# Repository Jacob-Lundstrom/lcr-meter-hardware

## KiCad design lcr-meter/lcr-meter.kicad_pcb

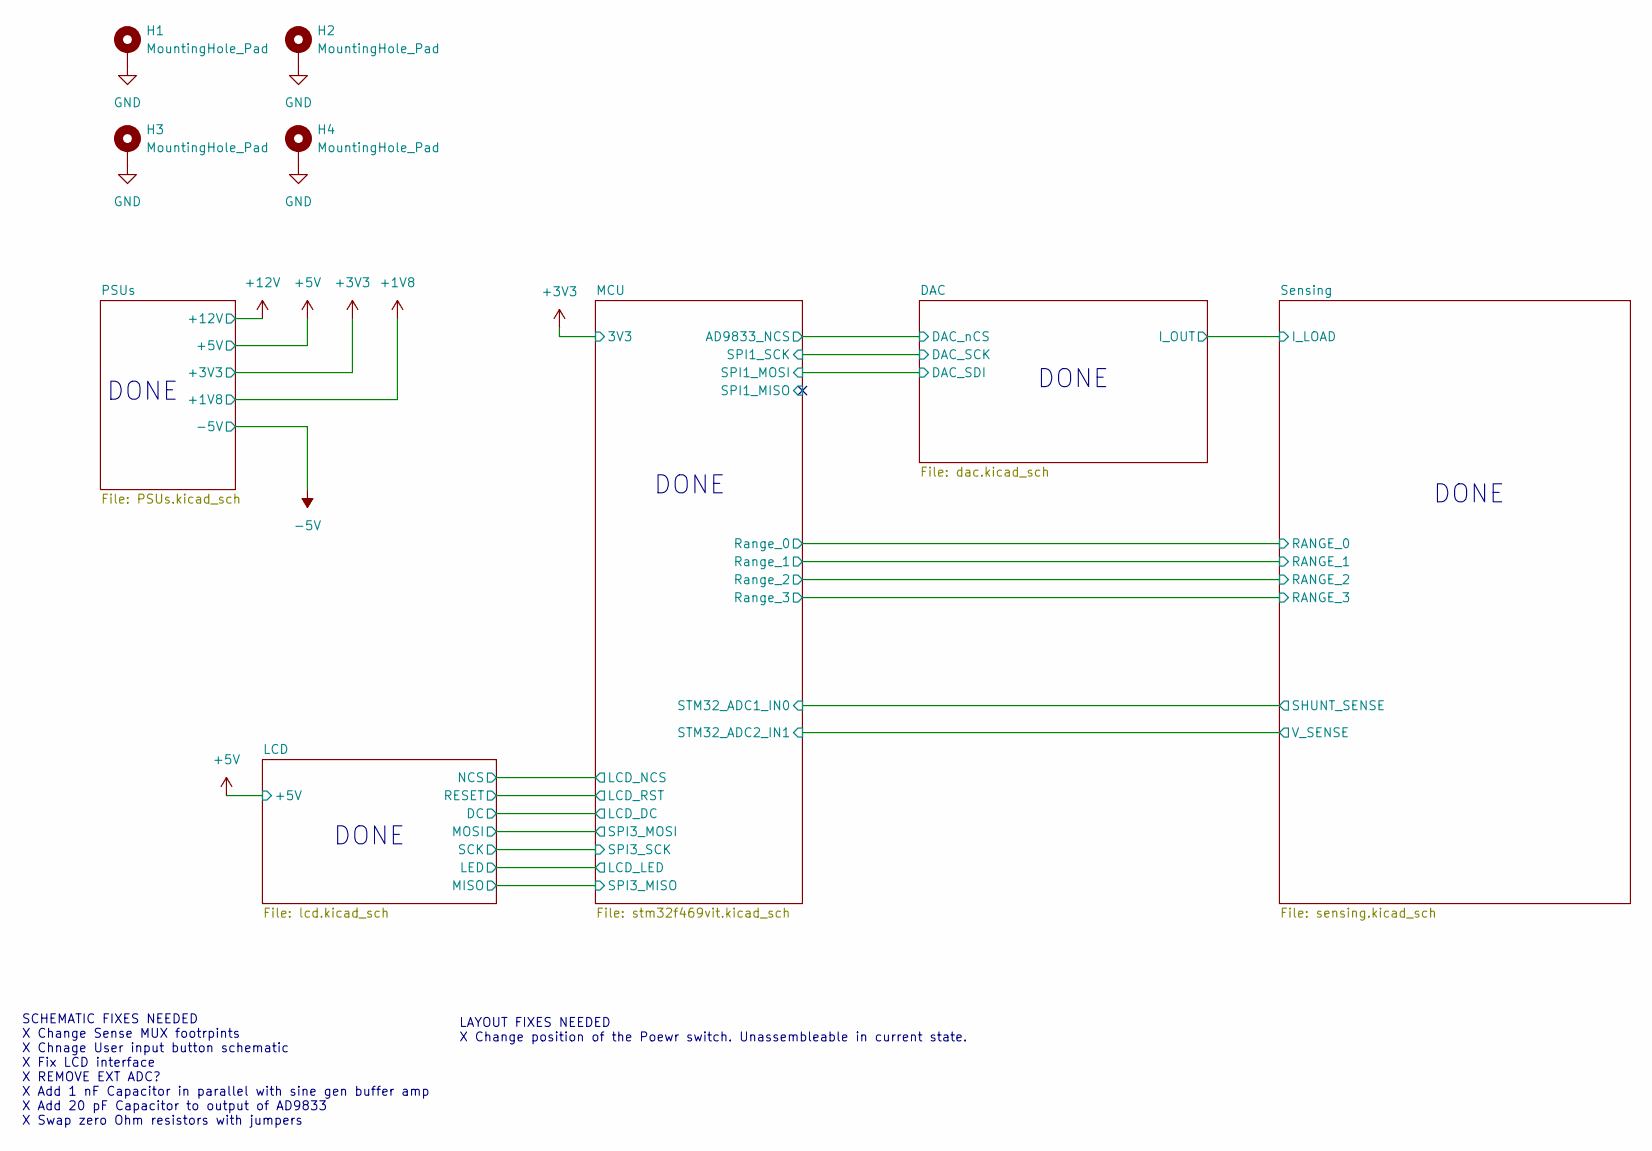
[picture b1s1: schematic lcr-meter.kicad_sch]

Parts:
H1, H2, H3, H4: MountingHole_Pad; MountingHole_3.2mm_M3_Pad_Via

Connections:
GND: H1.1, H2.1, H3.1, H4.1; also elsewhere on the board

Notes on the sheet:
DONE
SCHEMATIC FIXES NEEDED X Change Sense MUX footrpints X Chnage User input button schematic X Fix LCD interface X REMOVE EXT ADC? X Add 1 nF Capacitor in parallel with sine gen buffer amp X Add 20 pF Capacitor to output of AD9833 X Swap zero Ohm resistors with jumpers
LAYOUT FIXES NEEDED X Change position of the Poewr switch. Unassembleable in current state.

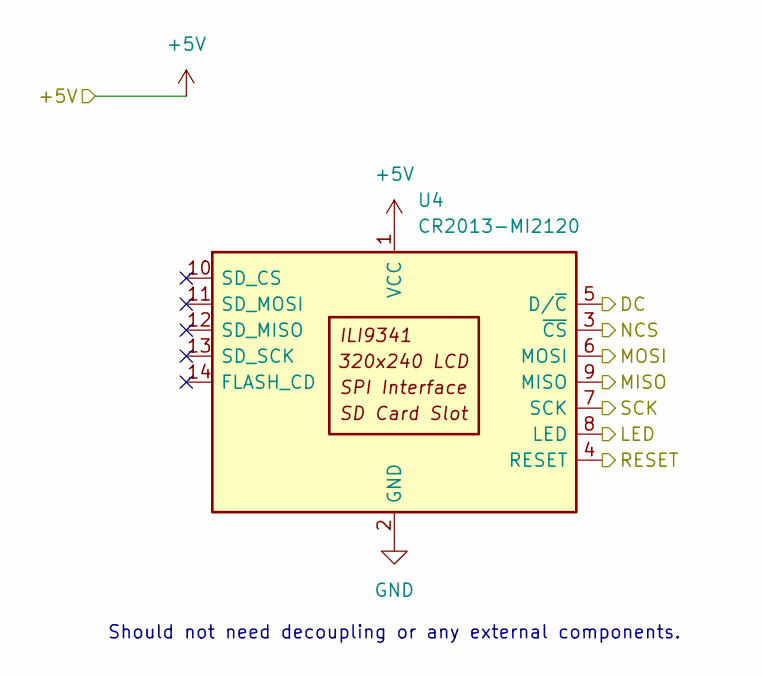
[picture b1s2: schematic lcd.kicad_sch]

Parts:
U4: CR2013-MI2120

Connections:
+5V: U4.1 (VCC); also elsewhere on the board
/LCD/DC: U4.5 (D/~C); also elsewhere on the board
/LCD/LED: U4.8 (LED); also elsewhere on the board
/LCD/MISO: U4.9 (MISO); also elsewhere on the board
/LCD/MOSI: U4.6 (MOSI); also elsewhere on the board
/LCD/NCS: U4.3 (~CS); also elsewhere on the board
/LCD/RESET: U4.4 (RESET); also elsewhere on the board
/LCD/SCK: U4.7 (SCK); also elsewhere on the board
GND: U4.2 (GND); also elsewhere on the board

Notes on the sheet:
Should not need decoupling or any external components.

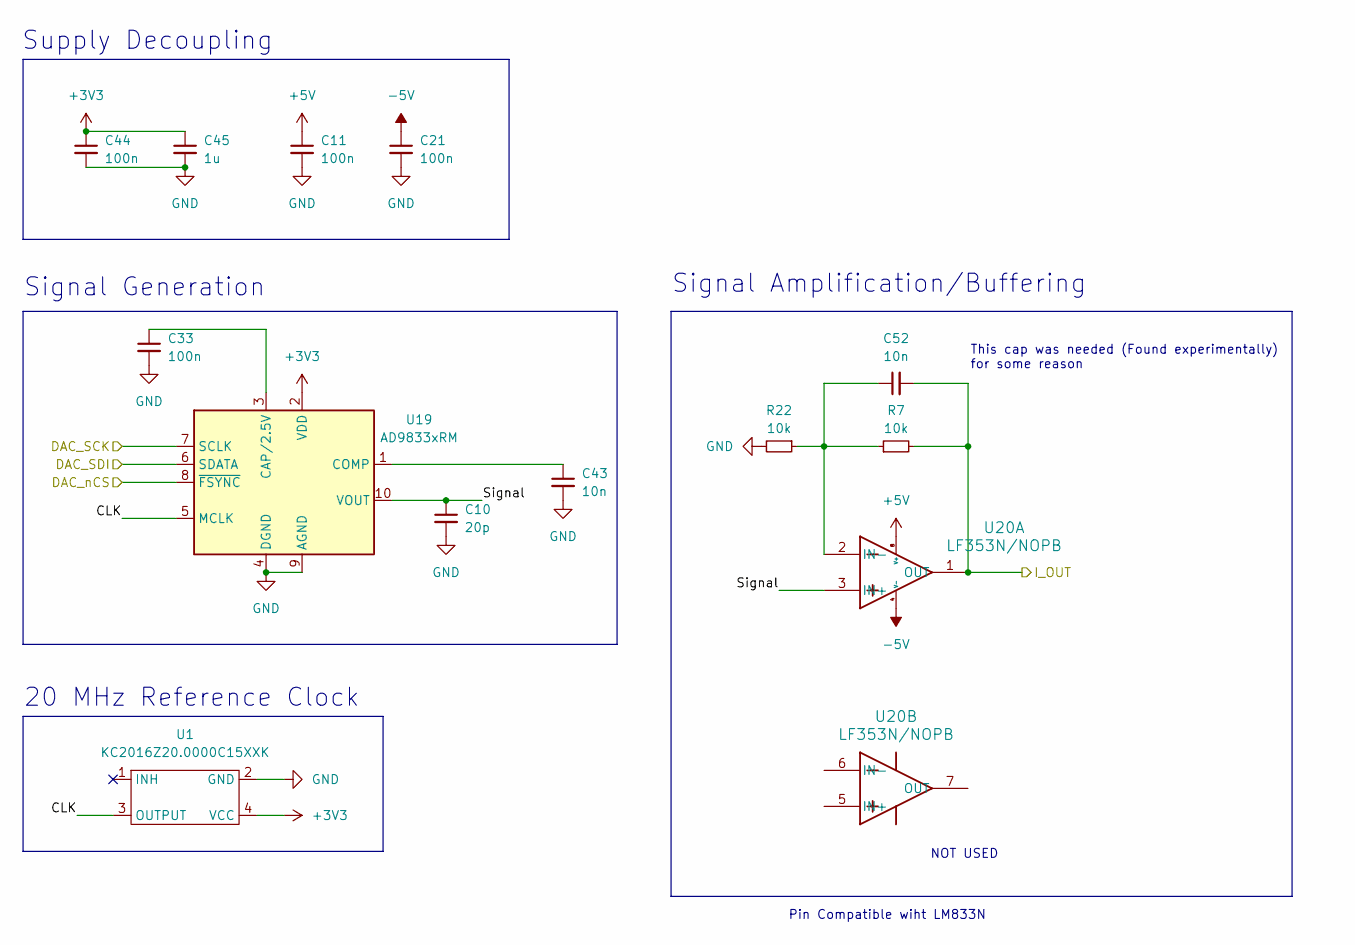
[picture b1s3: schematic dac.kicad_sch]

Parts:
C10: 20p; C_0402_1005Metric
C11, C21, C33, C44: 100n; C_0402_1005Metric
C43, C52: 10n; C_0402_1005Metric
C45: 1u; C_0402_1005Metric
R7, R22: 10k; R_0402_1005Metric
U1: KC2016Z20.0000C15XXK; Crystal_SMD_2016-4Pin_2.0x1.6mm
U19: AD9833xRM; MSOP-10_3x3mm_P0.5mm
U20: LF353N/NOPB; DIP-8_W7.62mm

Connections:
+3V3: C44.1, C45.1, U1.4 (VCC), U19.2 (VDD); also elsewhere on the board
+5V: C11.1, U20.8 (V+); also elsewhere on the board
-5V: C21.1, U20.4 (V-); also elsewhere on the board
/DAC/CLK: U1.3 (OUTPUT), U19.5 (MCLK)
/DAC/DAC_SCK: U19.7 (SCLK); also elsewhere on the board
/DAC/DAC_SDI: U19.6 (SDATA); also elsewhere on the board
/DAC/DAC_nCS: U19.8 (~FSYNC); also elsewhere on the board
/DAC/I_OUT: C52.2, R7.2, U20.1 (OUT); also elsewhere on the board
/DAC/Signal: C10.1, U19.10 (VOUT), U20.3 (IN+)
GND: C10.2, C11.2, C21.2, C33.2, C43.2, C44.2, C45.2, R22.2, U1.2 (GND), U19.4 (DGND), U19.9 (AGND); also elsewhere on the board
unnamed: C33.1, U19.3 (CAP/2.5V)
unnamed: C43.1, U19.1 (COMP)
unnamed: C52.1, R7.1, R22.1, U20.2 (IN-)

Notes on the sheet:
Pin Compatible wiht LM833N
20 MHz Reference Clock
This cap was needed (Found experimentally) for some reason
Supply Decoupling
Signal Generation
NOT USED
Signal Amplification/Buffering

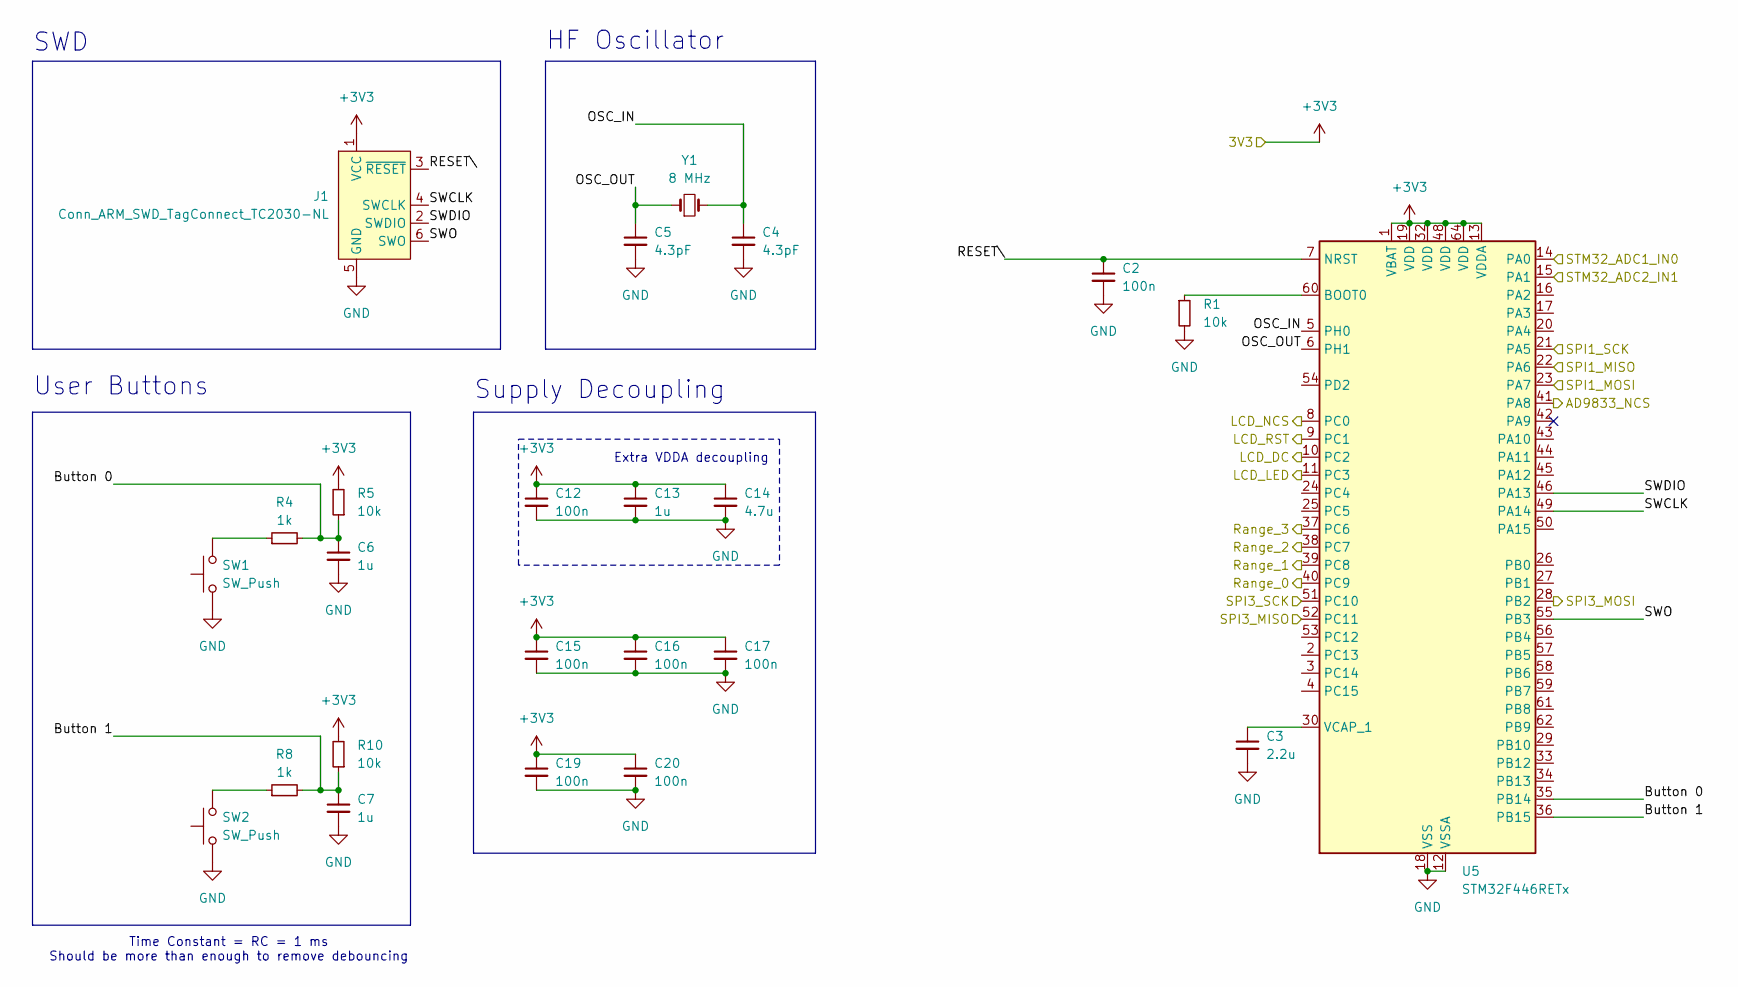
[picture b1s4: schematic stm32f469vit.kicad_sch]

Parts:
C2, C12, C15, C16, C17, C19, C20: 100n; C_0402_1005Metric
C3: 2.2u; C_0402_1005Metric
C4, C5: 4.3pF; C_0402_1005Metric
C6, C7, C13: 1u; C_0402_1005Metric
C14: 4.7u; C_0805_2012Metric
J1: Conn_ARM_SWD_TagConnect_TC2030-NL; Tag-Connect_TC2030-IDC-NL_2x03_P1.27mm_Vertical
R1, R5, R10: 10k; R_0402_1005Metric
R4, R8: 1k; R_0402_1005Metric
SW1, SW2: SW_Push; SW_PUSH_6mm_H5mm
U5: STM32F446RETx; LQFP-64_10x10mm_P0.5mm
Y1: 8 MHz; XTAL_CG04874_NDK-L

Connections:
+3V3: C12.1, C13.1, C14.1, C15.1, C16.1, C17.1, C19.1, C20.1, J1.1 (VCC), R5.2, R10.2, U5.1 (VBAT), U5.13 (VDDA), U5.19 (VDD), U5.32 (VDD), U5.48 (VDD), U5.64 (VDD); also elsewhere on the board
/DAC/DAC_SCK: U5.21 (PA5); also elsewhere on the board
/DAC/DAC_SDI: U5.23 (PA7); also elsewhere on the board
/DAC/DAC_nCS: U5.41 (PA8); also elsewhere on the board
/LCD/DC: U5.10 (PC2); also elsewhere on the board
/LCD/LED: U5.11 (PC3); also elsewhere on the board
/LCD/MISO: U5.52 (PC11); also elsewhere on the board
/LCD/MOSI: U5.28 (PB2); also elsewhere on the board
/LCD/NCS: U5.8 (PC0); also elsewhere on the board
/LCD/RESET: U5.9 (PC1); also elsewhere on the board
/LCD/SCK: U5.51 (PC10); also elsewhere on the board
/MCU/Button 0: C6.1, R4.2, R5.1, U5.35 (PB14)
/MCU/Button 1: C7.1, R8.2, R10.1, U5.36 (PB15)
/MCU/OSC_IN: C4.1, U5.5 (PH0), Y1.2
/MCU/OSC_OUT: C5.1, U5.6 (PH1), Y1.1
/MCU/RESET\: C2.1, J1.3 (~RESET), U5.7 (NRST)
/MCU/Range_0: U5.40 (PC9); also elsewhere on the board
/MCU/Range_1: U5.39 (PC8); also elsewhere on the board
/MCU/Range_2: U5.38 (PC7); also elsewhere on the board
/MCU/Range_3: U5.37 (PC6); also elsewhere on the board
/MCU/SPI1_MISO: U5.22 (PA6)
/MCU/STM32_ADC1_IN0: U5.14 (PA0); also elsewhere on the board
/MCU/STM32_ADC2_IN1: U5.15 (PA1); also elsewhere on the board
/MCU/SWCLK: J1.4 (SWCLK), U5.49 (PA14)
/MCU/SWDIO: J1.2 (SWDIO), U5.46 (PA13)
/MCU/SWO: J1.6 (SWO), U5.55 (PB3)
GND: C2.2, C3.2, C4.2, C5.2, C6.2, C7.2, C12.2, C13.2, C14.2, C15.2, C16.2, C17.2, C19.2, C20.2, J1.5 (GND), R1.2, SW1.1, SW2.1, U5.12 (VSSA), U5.18 (VSS), U5.31 (VSS), U5.47 (VSS), U5.63 (VSS); also elsewhere on the board
unnamed: R4.1, SW1.2
unnamed: R8.1, SW2.2
unnamed: R1.1, U5.60 (BOOT0)
unnamed: C3.1, U5.30 (VCAP_1)

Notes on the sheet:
Extra VDDA decoupling
Supply Decoupling
SWD
HF Oscillator
User Buttons
Time Constant = RC = 1 ms Should be more than enough to remove debouncing

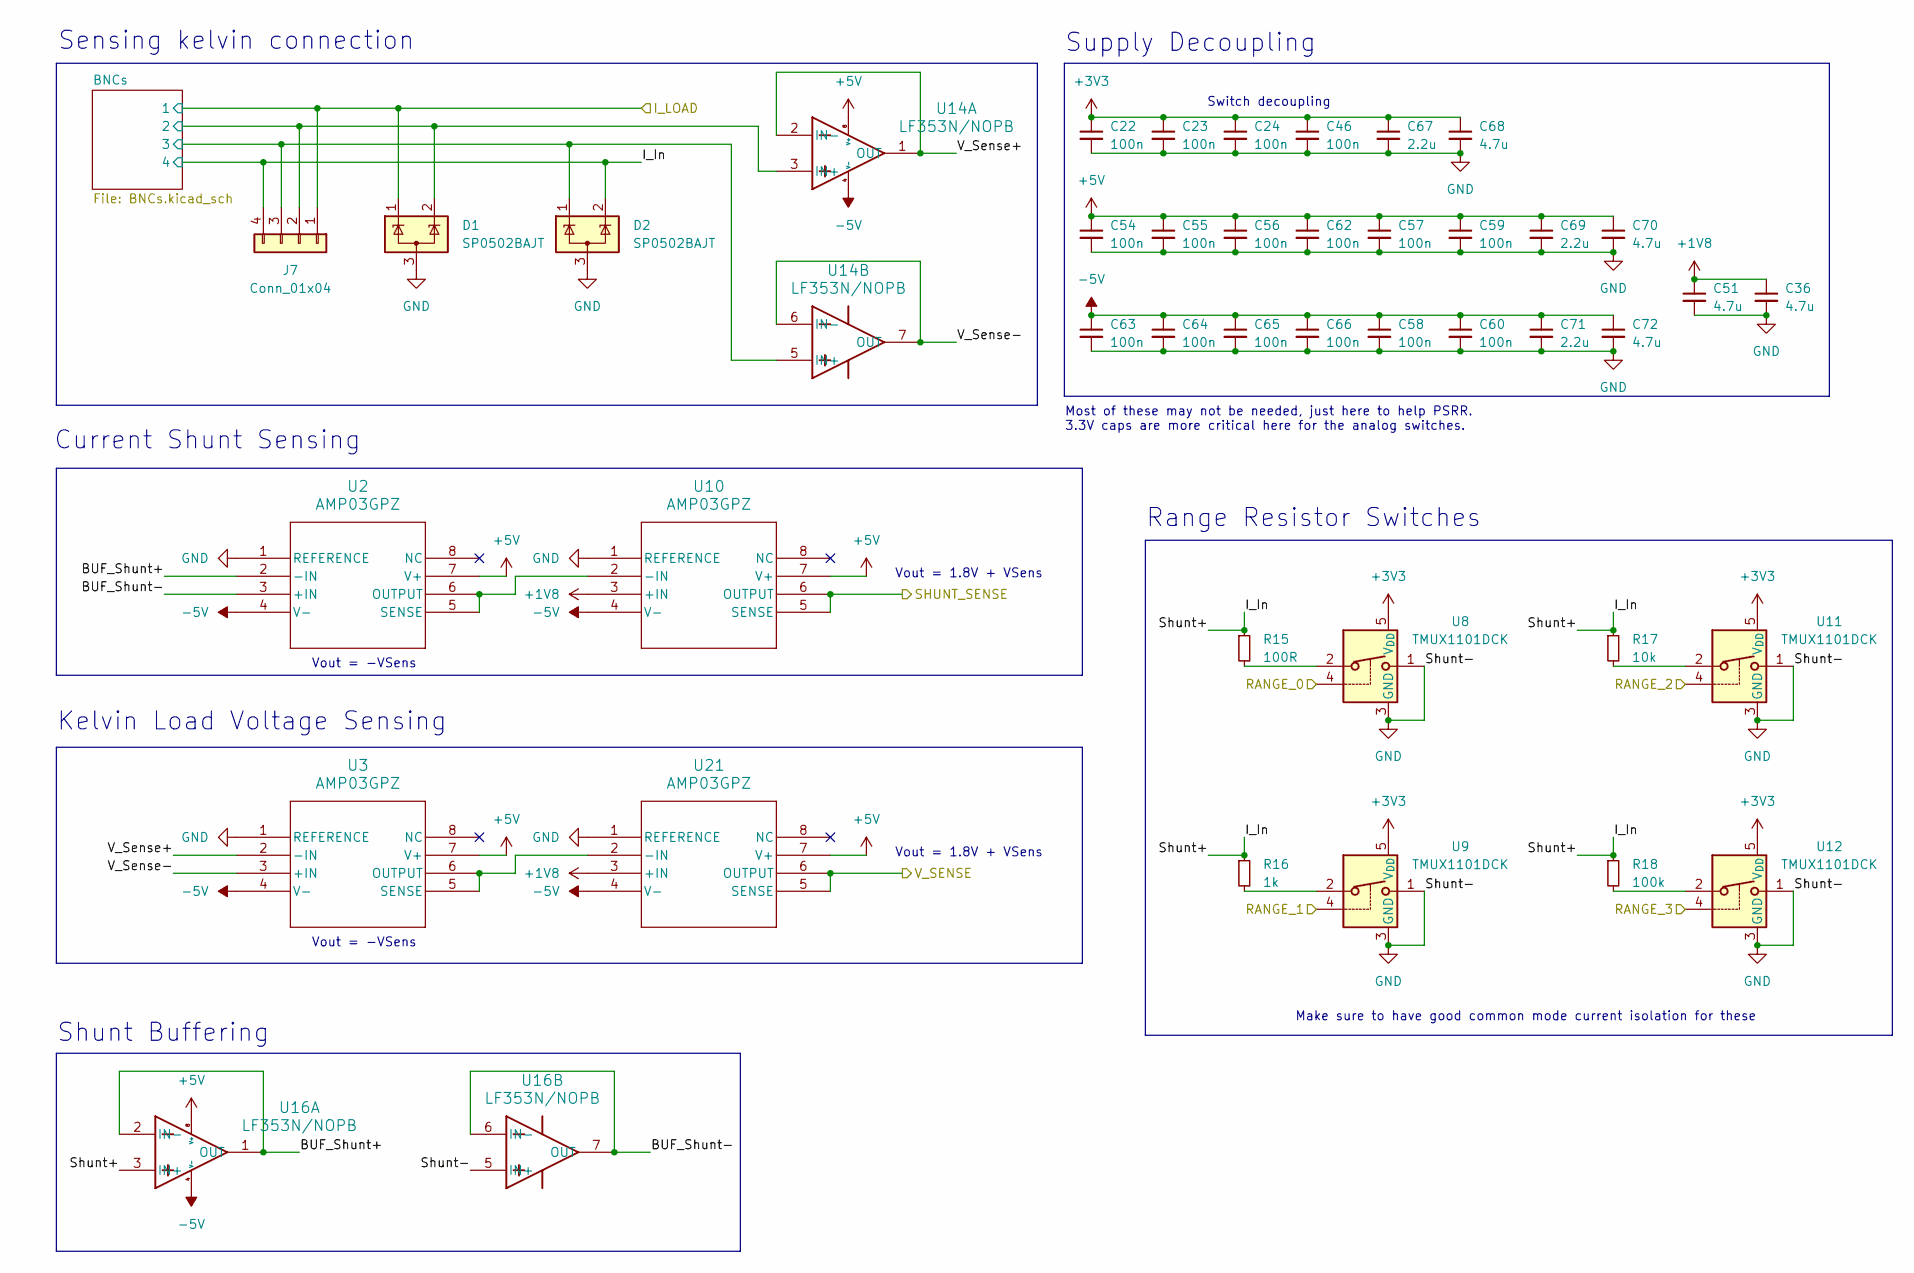
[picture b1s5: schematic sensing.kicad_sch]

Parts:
C22, C23, C24, C46, C54, C55, C56, C57, C58, C59, C60, C62, C63, C64, C65, C66: 100n; C_0402_1005Metric
C36, C51, C68, C70, C72: 4.7u; C_0805_2012Metric
C67, C69, C71: 2.2u; C_0402_1005Metric
D1, D2: SP0502BAJT; SOT-323_SC-70
J7: Conn_01x04; PinHeader_1x04_P2.54mm_Vertical
R15: 100R; R_0402_1005Metric
R16: 1k; R_0402_1005Metric
R17: 10k; R_0402_1005Metric
R18: 100k; R_0402_1005Metric
U2, U3, U10, U21: AMP03GPZ; N_8_ADI
U8, U9, U11, U12: TMUX1101DCK; SOT-353_SC-70-5
U14, U16: LF353N/NOPB; DIP-8_W7.62mm

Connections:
+1V8: C36.1, C51.1, U10.3 (+IN), U21.3 (+IN); also elsewhere on the board
+3V3: C22.1, C23.1, C24.1, C46.1, C67.1, C68.1, U8.5 (V_{DD}), U9.5 (V_{DD}), U11.5 (V_{DD}), U12.5 (V_{DD}); also elsewhere on the board
+5V: C54.1, C55.1, C56.1, C57.1, C59.1, C62.1, C69.1, C70.1, U2.7 (V+), U3.7 (V+), U10.7 (V+), U14.8 (V+), U16.8 (V+), U21.7 (V+); also elsewhere on the board
-5V: C58.1, C60.1, C63.1, C64.1, C65.1, C66.1, C71.1, C72.1, U2.4 (V-), U3.4 (V-), U10.4 (V-), U14.4 (V-), U16.4 (V-), U21.4 (V-); also elsewhere on the board
/DAC/I_OUT: D1.1 (K), J7.1; also elsewhere on the board
/MCU/Range_0: U8.4; also elsewhere on the board
/MCU/Range_1: U9.4; also elsewhere on the board
/MCU/Range_2: U11.4; also elsewhere on the board
/MCU/Range_3: U12.4; also elsewhere on the board
/MCU/STM32_ADC1_IN0: U10.5 (SENSE), U10.6 (OUTPUT); also elsewhere on the board
/MCU/STM32_ADC2_IN1: U21.5 (SENSE), U21.6 (OUTPUT); also elsewhere on the board
/Sensing/BNCs/2: D1.2 (K), J7.2, U14.3 (IN+); also elsewhere on the board
/Sensing/BNCs/3: D2.1 (K), J7.3, U14.5 (IN+); also elsewhere on the board
/Sensing/BUF_Shunt+: U2.2 (-IN), U16.1 (OUT), U16.2 (IN-)
/Sensing/BUF_Shunt-: U2.3 (+IN), U16.6 (IN-), U16.7 (OUT)
/Sensing/I_In: D2.2 (K), J7.4, R15.1, R16.1, R17.1, R18.1, U16.3 (IN+); also elsewhere on the board
/Sensing/V_Sense+: U3.2 (-IN), U14.1 (OUT), U14.2 (IN-)
/Sensing/V_Sense-: U3.3 (+IN), U14.6 (IN-), U14.7 (OUT)
GND: C22.2, C23.2, C24.2, C36.2, C46.2, C51.2, C54.2, C55.2, C56.2, C57.2, C58.2, C59.2, C60.2, C62.2, C63.2, C64.2, C65.2, C66.2, C67.2, C68.2, C69.2, C70.2, C71.2, C72.2, D1.3 (A), D2.3 (A), U2.1 (REFERENCE), U3.1 (REFERENCE), U8.1, U8.3 (GND), U9.1, U9.3 (GND), U10.1 (REFERENCE), U11.1, U11.3 (GND), U12.1, U12.3 (GND), U16.5 (IN+), U21.1 (REFERENCE); also elsewhere on the board
unnamed: R15.2, U8.2
unnamed: R16.2, U9.2
unnamed: R17.2, U11.2
unnamed: R18.2, U12.2
unnamed: U2.5 (SENSE), U2.6 (OUTPUT), U10.2 (-IN)
unnamed: U3.5 (SENSE), U3.6 (OUTPUT), U21.2 (-IN)

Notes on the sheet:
Make sure to have good common mode current isolation for these
Sensing kelvin connection
Vout = 1.8V + VSens
Vout = -VSens
Shunt Buffering
Current Shunt Sensing
Most of these may not be needed, just here to help PSRR. 3.3V caps are more critical here for the analog switches.
Range Resistor Switches
Supply Decoupling
Kelvin Load Voltage Sensing
Switch decoupling

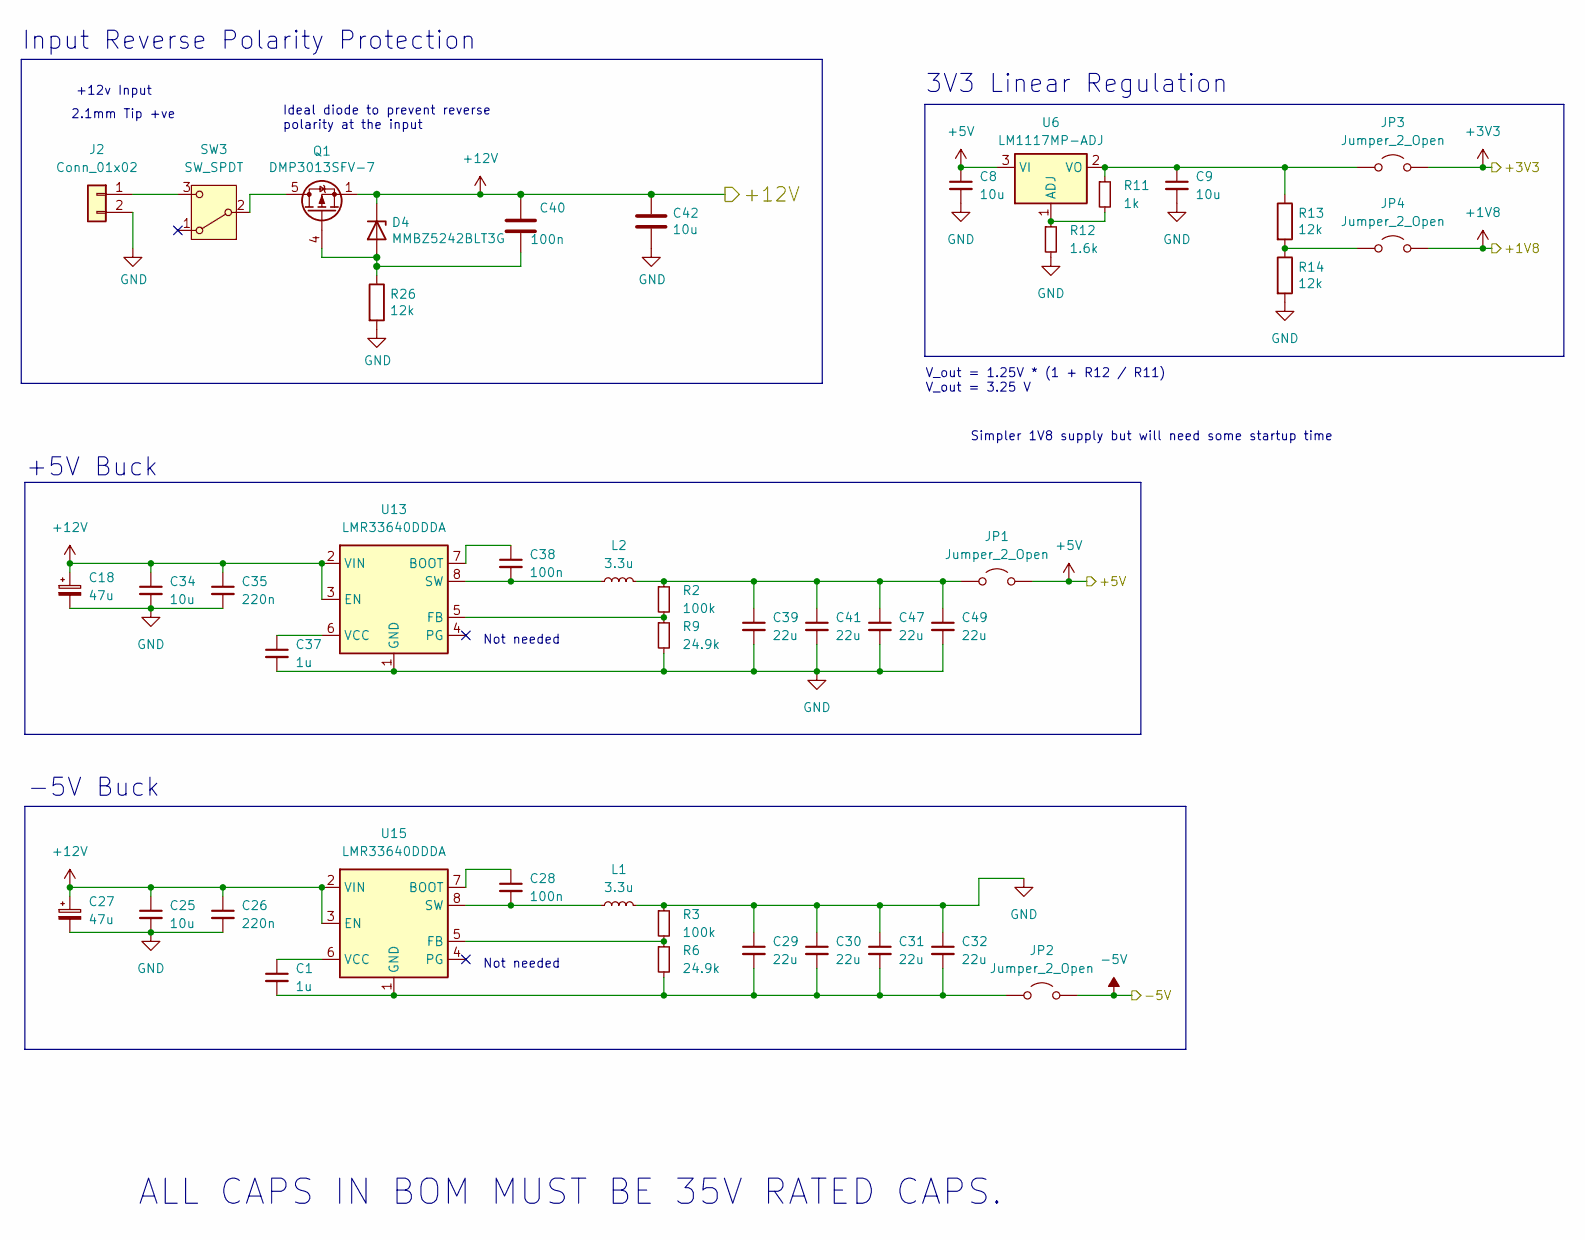
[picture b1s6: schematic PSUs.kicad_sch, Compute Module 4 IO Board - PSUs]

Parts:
C1, C37: 1u; C_0402_1005Metric
C8, C9, C25, C34: 10u; C_0805_2012Metric
C18, C27: 47u; CP_Elec_6.3x7.7
C26, C35: 220n; C_0402_1005Metric
C28, C38: 100n; C_0402_1005Metric
C29, C30, C31, C32, C39, C41, C47, C49: 22u; C_0805_2012Metric
C40: 100n; C_0402_1005Metric; Part Description 0.1uF 10% 16V Ceramic Capacitor X7R 040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
C42: 10u; C_0805_2012Metric; Part Description 10uF 10% or 20% 35V Ceramic Capacitor X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
D4: MMBZ5242BLT3G; SOT-23; Part Description Zener Diode 12V 225mW 5% Surface Mount 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
J2: Conn_01x02; PinHeader_1x02_P2.54mm_Vertical
JP1, JP2, JP3, JP4: Jumper_2_Open; SolderJumper-2_P1.3mm_Open_TrianglePad1.0x1.5mm
L1, L2: 3.3u; IND_223NLT_PUL
Q1: DMP3013SFV-7; Diodes_PowerDI3333-8; Part Description DMP3013SFV-7 - Power MOSFET, P Channel,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
R2, R3: 100k; R_0402_1005Metric
R6, R9: 24.9k; R_0402_1005Metric
R11: 1k; R_0402_1005Metric
R12: 1.6k; R_0402_1005Metric
R13, R14, R26: 12k; R_0402_1005Metric; Part Description Resistor 12K M1005 1% 63mW
SW3: SW_SPDT; SW_E-Switch_EG1224_SPDT_Angled
U6: LM1117MP-ADJ; SOT-223-3_TabPin2
U13, U15: LMR33640DDDA; Texas_HSOP-8-1EP_3.9x4.9mm_P1.27mm_ThermalVias

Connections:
+1V8: JP4.2 (B); also elsewhere on the board
+3V3: JP3.2 (B); also elsewhere on the board
+5V: C8.1, JP1.2 (B), U6.3 (VI); also elsewhere on the board
+12V: C18.1, C25.1, C26.1, C27.1, C34.1, C35.1, C40.1, C42.1, D4.3 (K), Q1.1 (S), Q1.2 (S), Q1.3 (S), U13.2 (VIN), U13.3 (EN), U15.2 (VIN), U15.3 (EN)
-5V: JP2.2 (B); also elsewhere on the board
GND: C8.2, C9.2, C18.2, C25.2, C26.2, C27.2, C29.1, C30.1, C31.1, C32.1, C34.2, C35.2, C37.2, C39.2, C41.2, C42.2, C47.2, C49.2, J2.2, L1.2, R3.1, R9.2, R12.2, R14.2, R26.2, U13.1 (GND), U13.9 (GND); also elsewhere on the board
unnamed: C40.2, D4.1 (A), Q1.4 (G), R26.1
unnamed: J2.1, SW3.3 (C)
unnamed: C39.1, C41.1, C47.1, C49.1, JP1.1 (A), L2.2, R2.1
unnamed: C1.2, C29.2, C30.2, C31.2, C32.2, JP2.1 (A), R6.2, U15.1 (GND), U15.9 (GND)
unnamed: C9.1, JP3.1 (A), R11.1, R13.1, U6.2 (VO)
unnamed: JP4.1 (A), R13.2, R14.1
unnamed: Q1.5 (D), SW3.2 (B)
unnamed: R11.2, R12.1, U6.1 (ADJ)
unnamed: C38.1, U13.7 (BOOT)
unnamed: R2.2, R9.1, U13.5 (FB)
unnamed: C38.2, L2.1, U13.8 (SW)
unnamed: C37.1, U13.6 (VCC)
unnamed: C28.1, U15.7 (BOOT)
unnamed: R3.2, R6.1, U15.5 (FB)
unnamed: C28.2, L1.1, U15.8 (SW)
unnamed: C1.1, U15.6 (VCC)

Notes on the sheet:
Not needed
Input Reverse Polarity Protection
V_out = 1.25V * (1 + R12 / R11) V_out = 3.25 V
+12v Input
-5V Buck
+5V Buck
3V3 Linear Regulation
2.1mm Tip +ve
ALL CAPS IN BOM MUST BE 35V RATED CAPS.
Simpler 1V8 supply but will need some startup time
Ideal diode to prevent reverse polarity at the input

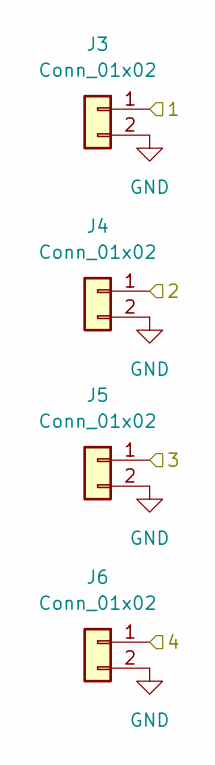
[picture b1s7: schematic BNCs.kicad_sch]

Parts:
J3, J4, J5, J6: Conn_01x02; 1-1337445-0

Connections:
/DAC/I_OUT: J3.1; also elsewhere on the board
/Sensing/BNCs/2: J4.1; also elsewhere on the board
/Sensing/BNCs/3: J5.1; also elsewhere on the board
/Sensing/I_In: J6.1; also elsewhere on the board
GND: J3.2, J4.2, J5.2, J6.2; also elsewhere on the board

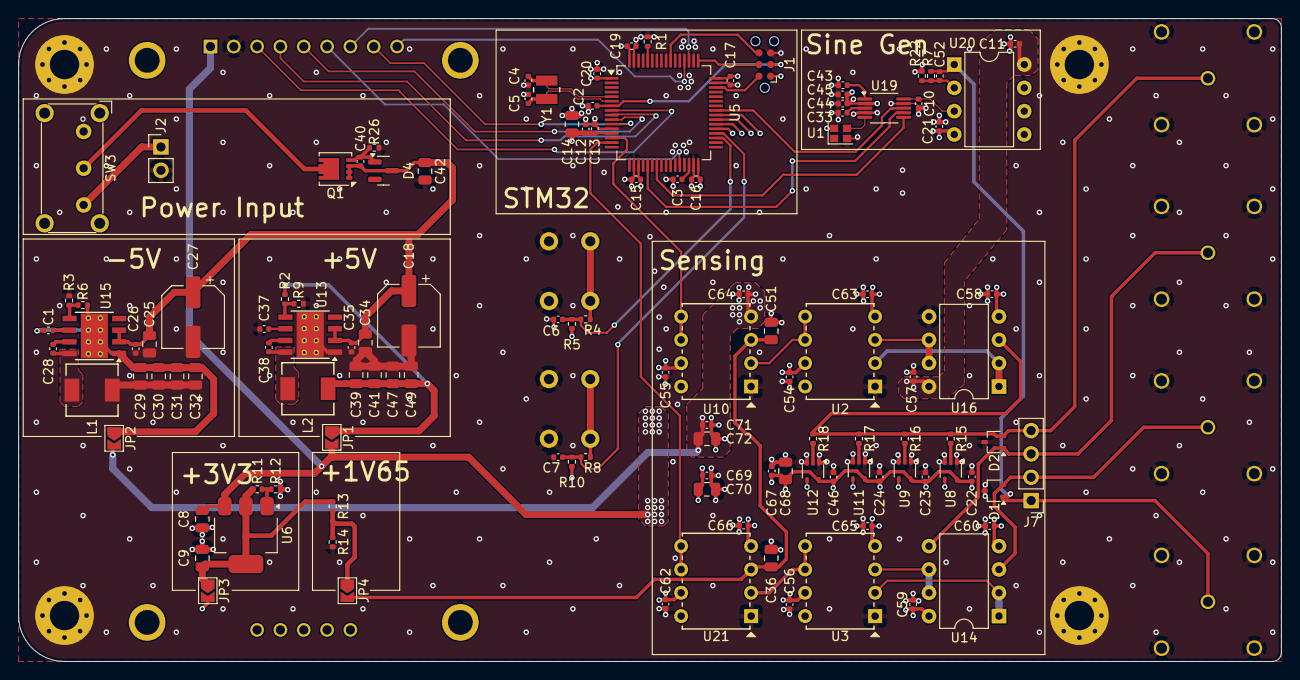
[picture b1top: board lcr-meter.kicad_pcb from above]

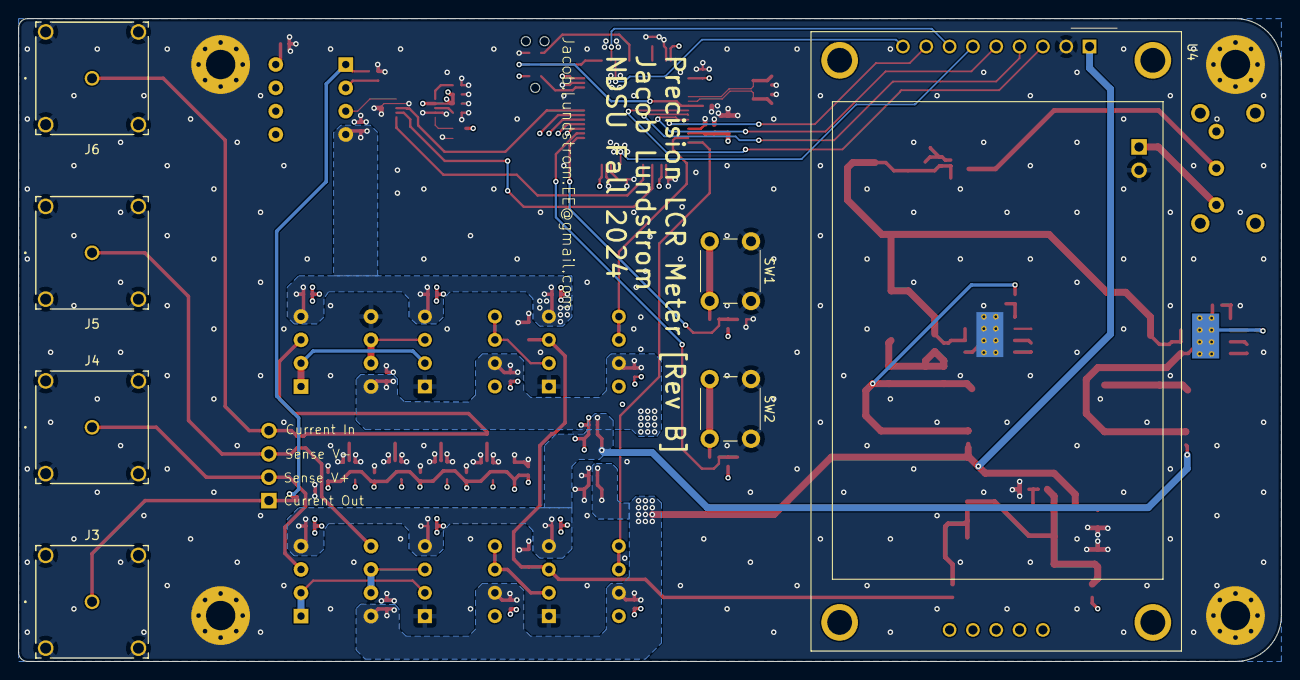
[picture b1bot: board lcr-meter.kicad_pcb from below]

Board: 4 copper layers, 137.5 x 70.0 mm, 131 parts (7 on the bottom side), 69 nets.

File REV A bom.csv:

?,Designator,Footprint,Quantity,Value,LCSC Part #,DigiKey Part #,MFG Part #,Notes
X,"C1, C13, C37, C45, C50, C6, C7",0402,7,1u,,,GRM155R61H105KE05D,
X,"C10, C11, C25, C34, C42, C8, C9",0805,7,10u,,,GRM21BR61H106KE43L,
X,"C12, C15, C16, C17, C19, C2, C20, C22, C23, C24, C28, C33, C38, C40, C44, C46, C48, C54, C55, C56, C62, C63, C64, C65, C66",0402,25,100n,,,GCM155R71H104KE02J,
X,"C14, C36, C51, C53, C68, C70, C72",0805,7,4.7u,,,GRM21BR61H475KE51L,
X,"C18, C27",CP_Elec_6.3x7.7,2,47u,,,8.65081E+11,
X,"C26, C35",0402,2,220n,,,GRM155R61J224KE01J,
X,"C29, C30, C31, C32, C39, C41, C47, C49",0805,8,22u,,,C2012X5R1V226M125AC,
X,"C3, C67, C69, C71",0402,4,2.2u,,,C1005X5R1V225K050BC,
X,"C4, C5",0402,2,4.3pF,,,GJM1555C1H4R3CB01D,
X,C43,0402,1,10n,,,GCM155R71H103KA55D,
X,"D1, D2",SOT-323_SC-70,2,SP0502BAJT,,,SP0502BAJTG,
X,D4,SOT-23,1,MMBZ5242BLT3G,,,MMBZ5242BLT3G,
X,J19,BarrelJack_Horizontal,1,Barrel_Jack,,,,DNP
X,J4,PinHeader_1x04_P2.54mm_Vertical,1,Conn_01x04,,,,DNP
X,"L1, L2",IND_223NLT_PUL,2,3.3u,,,PA4340.332ANLT,
X,Q1,Diodes_PowerDI3333-8,1,DMP3013SFV-7,,,DMP3013SFV-7,
X,"R1, R10, R17, R22, R5, R7",0402,6,10k,,,RNCF0402TKY10K0,
X,"R11, R14, R16, R4, R8",0402,5,1k,,,RNCF0402TKY1K00,
X,R12,0402,1,1.6k,,,RC0402FR-071K6L,
X,R13,0402,1,500R,,,RT0402FRE07500RL,
X,R15,0402,1,100R,,,RNCF0402TKY100R,
X,"R18, R2, R3",0402,3,100k,,,TNPU0402100KAYEP00,
,"R19, R20, R21, R23",0402,4,0R,,,RC0402JR-070RL,
X,R26,0402,1,12K 1%,,,RC0402FR-0712KL,
X,"R6, R9",0402,2,24.9k,,,RC0402FR-0724K9L,
,"SW1, SW2",SW_PUSH_6mm_H5mm,2,SW_Push,,,,Already purchased
,SW3,SW_E-Switch_EG1224_SPDT_Angled,1,SW_SPDT,,,EG1224,
X,U1,Crystal_SMD_2016-4Pin_2.0x1.6mm,1,KC2016Z20.0000C15XXK,,,KC2016Z20.0000C15XXK,
,"U10, U2, U21, U3",N_8_ADI,4,AMP03GPZ,,,AMP03GPZ,
X,"U11, U12, U8, U9",SOT-23-5,4,TMUX1101DCK,,,TMUX1101DCKR,
X,"U13, U15",Texas_HSOP-8-1EP_3.9x4.9mm_P1.27mm_ThermalVias,2,LMR33640DDDA,,,LMR33640DDDAR,
,U17,DIP-8_W7.62mm,1,MCP3202,,,MCP3202-CI/P,
X,U19,MSOP-10_3x3mm_P0.5mm,1,AD9833xRM,,,AD9833BRMZ,
,U20,DIP-8_W7.62mm,1,LF353N/NOPB,,,LM833N/NOPB,
,U4,CR2013-MI2120,1,CR2013-MI2120,,,,Random amazon TFT that fit the footprint
X,U5,LQFP-64_10x10mm_P0.5mm,1,STM32F446RETx,,,STM32F446RET6TR,
X,"U6, U7",SOT-223-3_TabPin2,2,LM1117MP-ADJ,,,LM1117MP-ADJ/NOPB,
X,Y1,XTAL_CG04874_NDK-L,1,8 MHz,,,CG04874-8M,

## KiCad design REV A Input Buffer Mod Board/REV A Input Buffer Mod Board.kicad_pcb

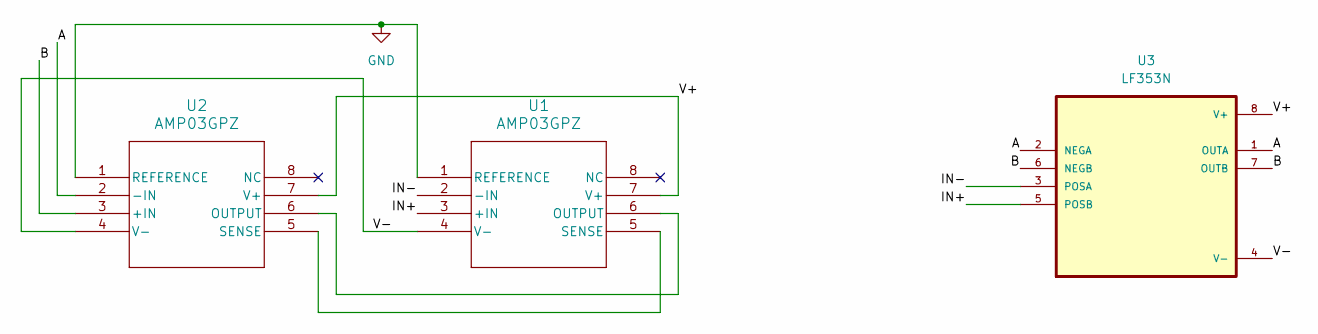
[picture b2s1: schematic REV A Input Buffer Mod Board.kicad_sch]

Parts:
U1, U2: AMP03GPZ; DIP-8_W7.62mm
U3: LF353N; DIP-8_W7.62mm

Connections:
/A: U2.2 (-IN), U3.1 (OUTA), U3.2 (NEGA)
/B: U2.3 (+IN), U3.6 (NEGB), U3.7 (OUTB)
/IN+: U1.3 (+IN), U3.5 (POSB)
/IN-: U1.2 (-IN), U3.3 (POSA)
/V+: U1.7 (V+), U2.7 (V+), U3.8 (V+)
/V-: U1.4 (V-), U2.4 (V-), U3.4 (V-)
GND: U1.1 (REFERENCE), U2.1 (REFERENCE)
unnamed: U1.6 (OUTPUT), U2.6 (OUTPUT)
unnamed: U1.5 (SENSE), U2.5 (SENSE)

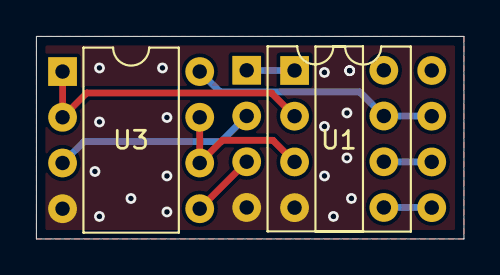
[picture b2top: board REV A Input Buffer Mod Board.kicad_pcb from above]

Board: 2 copper layers, 23.8 x 11.2 mm, 3 parts (0 on the bottom side), 9 nets.

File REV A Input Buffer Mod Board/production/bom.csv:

Designator,Footprint,Quantity,Value,LCSC Part #
"U1, U2",DIP-8_W7.62mm,2,AMP03GPZ,
U3,DIP-8_W7.62mm,1,LF353N,

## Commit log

2024-09-09 Basic Block Diagram started
2024-09-10 Added CM4, basics of functionality started
2024-09-10 Progress, removal of unnecessary components
2024-10-06 Breadboarding notes
2024-10-13 Schematic updates, added -5V, finalized sensing
2024-10-15 Addressable LED test board
2024-10-21 Schematic polishing, starting MCU schematic
2024-10-26 Schematic completion
2024-10-27 Schematic polishing
2024-10-27 Component grouping started
2024-10-27 Component grouping completed
2024-10-28 Order submitteed, Mod board submitted
2024-10-29 Rev A schematic fixes
2024-11-07 PCB updates
2024-11-07 Rev B Fixes
2024-11-10 REV B order submitted
2024-11-14 Added Rev B BOM
2024-12-29 Polishing, Poster Creation

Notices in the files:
lcr-meter/PSUs.kicad_sch:
© 2020-2022 Raspberry Pi Ltd (formerly Raspberry Pi (Trading) Ltd.)
parts and their libraries:
Copyright 2016 Accelerated Designs. All rights reserved.
